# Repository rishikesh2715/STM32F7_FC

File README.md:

# I am going to be working on a new design of this flight controller.

- Removing AT7456E based analog OSD and CVBS routing.
- Targeting modern digital FPV systems.
- Feel free to recommend any changes you wanna see. Just open an issue.

Hoping to have the new hardware done next month if life chills out. 

# STM32F7_Based_FLight-controller
STM32F722RET6 Based Flight Controller with ICM-42688-P IMU, BMP388 Barometer, and much more!

Detailed Specification:
- MCU - STM32F722RET6
- Interial Measurement Unit (IMU) - ICM-42688-P
- Barometer - BMP388
- On-screen Display chip (OSD) - AT7456E
- SPI FLASH - W25Q256JVEIQ (256 Mbit QUAD SPI NOR FLASH)
- 9 V -- 2A Buck Converter - TPS54335ADRCR
- 5V -- 2A Buck Converter - TPS54335ADRCR
- 3.3 V -- 700 mA LDO - AZ1117-3.3

Connectors:
- 4 UARTs
- 3 SPIs
- 1 I2C

This flight controller is directly flashable and configurale via BetaFlight. Make sure to flash the FC with custom CLI file named "IRS_CLI". There is a official tutorial on youtube on how to flash a custom flight controller with a custom cli file.

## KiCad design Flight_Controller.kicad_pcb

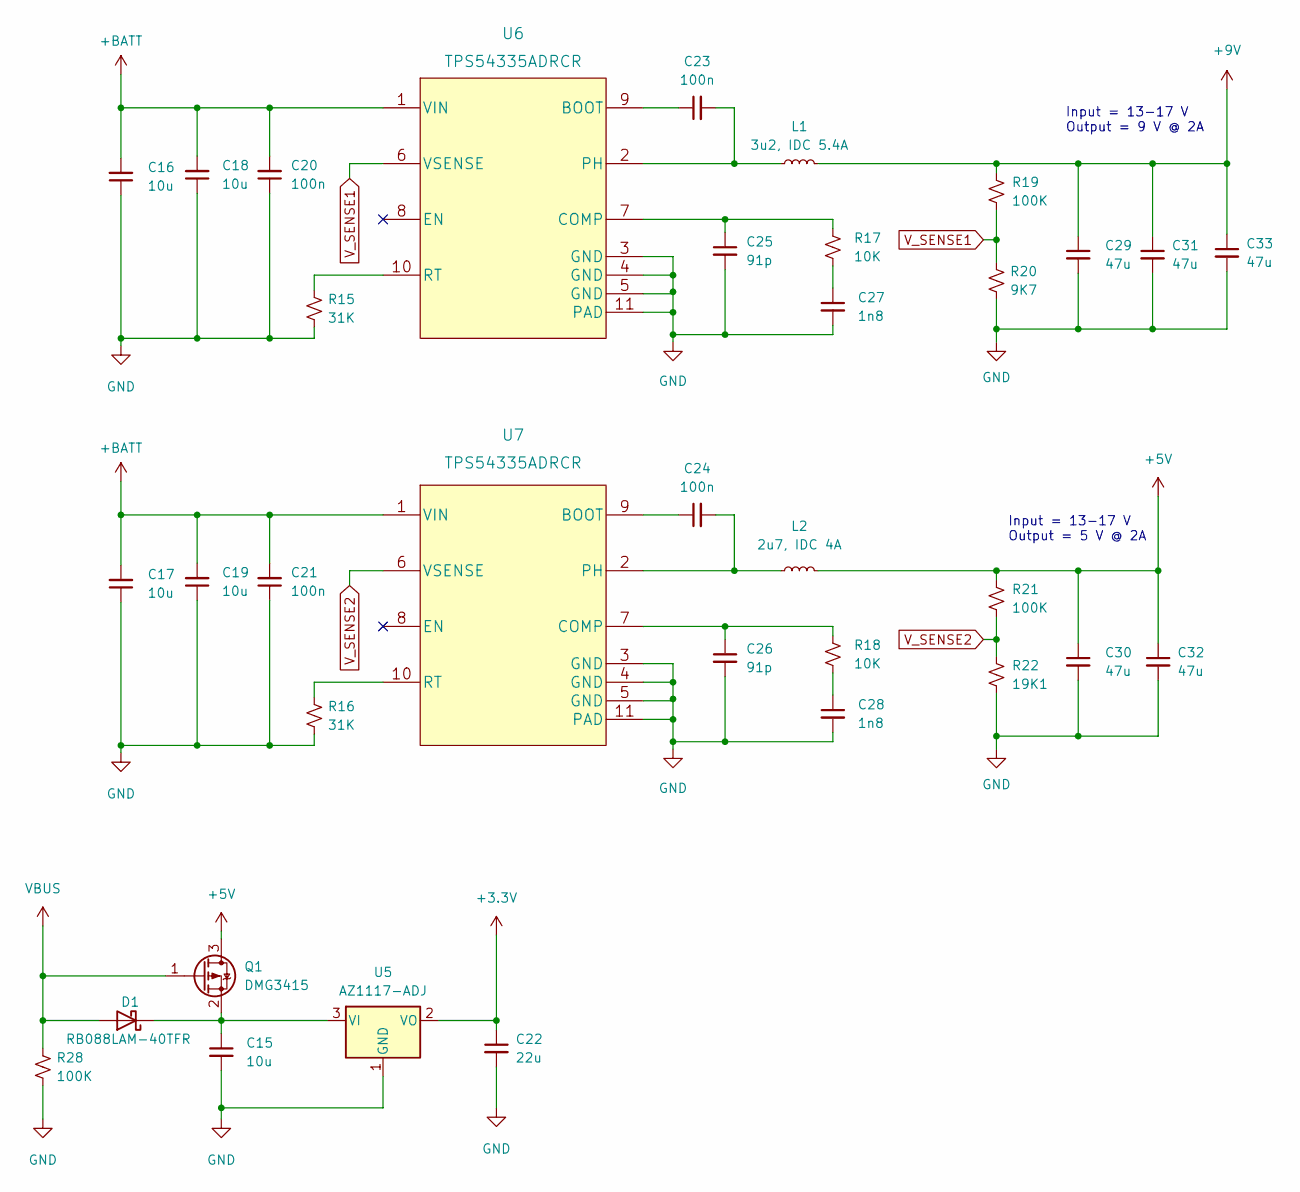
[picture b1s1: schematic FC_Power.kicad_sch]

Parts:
C15, C16, C17, C18, C19: 10u; C_0805_2012Metric
C20, C21, C23, C24: 100n; C_0402_1005Metric
C22: 22u; C_0805_2012Metric
C25, C26: 91p; C_0201_0603Metric
C27, C28: 1n8; C_0603_1608Metric
C29, C30, C31, C32, C33: 47u; C_1210_3225Metric
D1: RB088LAM-40TFR; D_SOD-123
L1: 3u2, IDC 5.4A; MDE0530-6R8M
L2: 2u7, IDC 4A; MDE0530-6R8M
Q1: DMG3415; SOT-23
R15, R16: 31K; R_0402_1005Metric
R17, R18: 10K; R_0402_1005Metric
R19: 100K; R_0402_1005Metric
R20: 9K7; R_0402_1005Metric
R21, R28: 100K; R_0201_0603Metric
R22: 19K1; R_0201_0603Metric
U5: AZ1117-ADJ; SOT-223-3_TabPin2
U6, U7: TPS54335ADRCR

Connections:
+3V3: C22.1, U5.2 (VO); also elsewhere on the board
+5V: C30.1, C32.1, L2.2, Q1.3 (D), R21.1; also elsewhere on the board
+9V: C29.1, C31.1, C33.1, L1.2, R19.1; also elsewhere on the board
+BATT: C16.2, C17.2, C18.2, C19.2, C20.2, C21.2, U6.1 (VIN), U7.1 (VIN); also elsewhere on the board
GND: C15.2, C16.1, C17.1, C18.1, C19.1, C20.1, C21.1, C22.2, C25.2, C26.2, C27.2, C28.2, C29.2, C30.2, C31.2, C32.2, C33.2, R15.2, R16.2, R20.2, R22.2, R28.2, U5.1 (GND), U6.3 (GND), U6.4 (GND), U6.5 (GND), U6.11 (PAD), U7.3 (GND), U7.4 (GND), U7.5 (GND), U7.11 (PAD); also elsewhere on the board
unnamed: C15.1, D1.1 (K), Q1.2 (S), U5.3 (VI)
unnamed: C23.1, U6.9 (BOOT)
unnamed: C23.2, L1.1, U6.2 (PH)
unnamed: C24.1, U7.9 (BOOT)
unnamed: C24.2, L2.1, U7.2 (PH)
unnamed: C25.1, R17.1, U6.7 (COMP)
unnamed: C26.1, R18.1, U7.7 (COMP)
unnamed: C27.1, R17.2
unnamed: C28.1, R18.2
unnamed: R15.1, U6.10 (RT)
unnamed: R16.1, U7.10 (RT)
VBUS: D1.2 (A), Q1.1 (G), R28.1; also elsewhere on the board
V_SENSE1: R19.2, R20.1, U6.6 (VSENSE)
V_SENSE2: R21.2, R22.1, U7.6 (VSENSE)

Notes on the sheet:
Input = 13-17 V Output = 9 V @ 2A
Input = 13-17 V Output = 5 V @ 2A

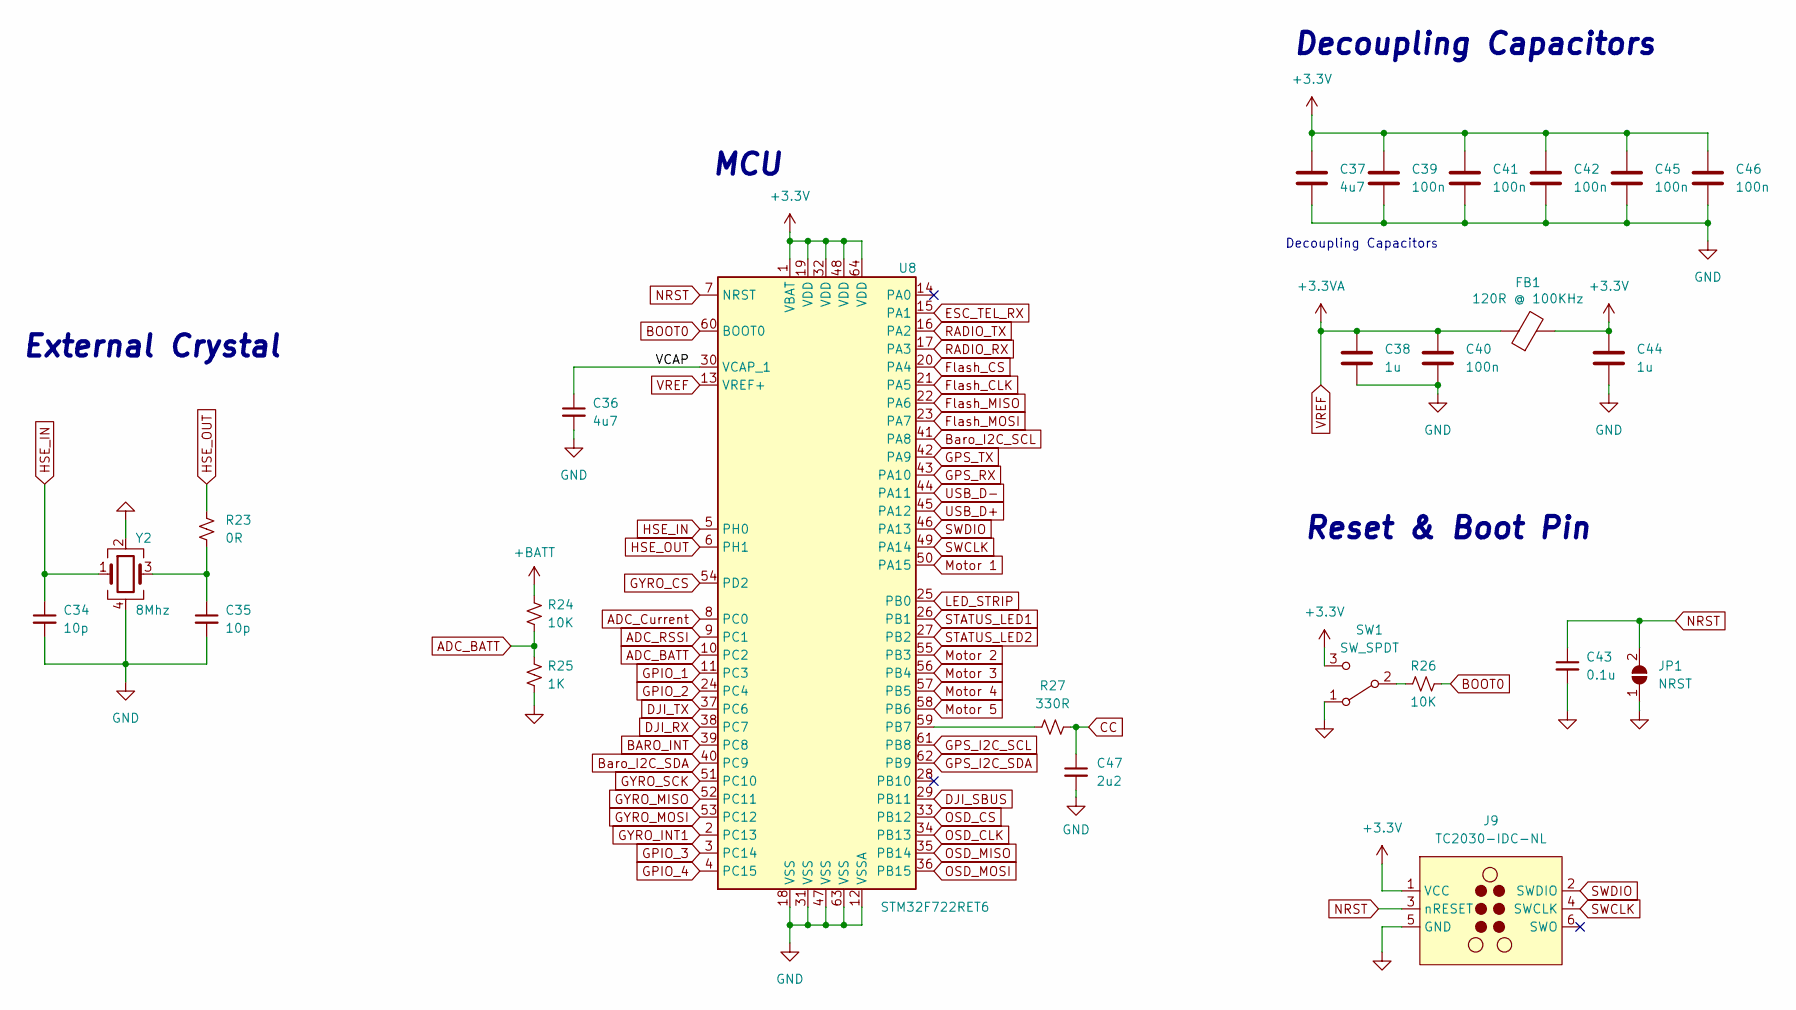
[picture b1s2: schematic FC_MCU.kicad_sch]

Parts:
C34, C35: 10p; C_0402_1005Metric
C36: 4u7; C_0603_1608Metric
C37: 4u7; C_0402_1005Metric
C38, C44: 1u; C_0402_1005Metric
C39, C40, C41, C42, C45, C46: 100n; C_0201_0603Metric
C43: 0.1u; C_0402_1005Metric
C47: 2u2; C_0603_1608Metric
FB1: 120R @ 100KHz; R_0603_1608Metric
J9: TC2030-IDC-NL; Tag-Connect_TC2030-IDC-NL_2x03_P1.27mm_Vertical
JP1: NRST; SolderJumper-2_P1.3mm_Open_TrianglePad1.0x1.5mm
R23: 0R; R_0402_1005Metric
R24: 10K; R_0201_0603Metric
R25: 1K; R_0201_0603Metric
R26: 10K; R_0402_1005Metric
R27: 330R; R_0603_1608Metric
SW1: SW_SPDT; SSSS810701
U8: STM32F722RET6; LQFP-64_10x10mm_P0.5mm
Y2: 8Mhz; Crystal_SMD_3225-4Pin_3.2x2.5mm

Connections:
+3V3: C37.1, C39.1, C41.1, C42.1, C44.1, C45.1, C46.1, FB1.2, J9.1 (VCC), SW1.3 (C), U8.1 (VBAT), U8.19 (VDD), U8.32 (VDD), U8.48 (VDD), U8.64 (VDD); also elsewhere on the board
+BATT: R24.1; also elsewhere on the board
/MCU/VCAP: C36.1, U8.30 (VCAP_1)
ADC_BATT: R24.2, R25.1, U8.10 (PC2)
ADC_Current: U8.8 (PC0); also elsewhere on the board
ADC_RSSI: U8.9 (PC1)
BARO_INT: U8.39 (PC8); also elsewhere on the board
BOOT0: R26.2, U8.60 (BOOT0)
Baro_I2C_SCL: U8.41 (PA8); also elsewhere on the board
Baro_I2C_SDA: U8.40 (PC9); also elsewhere on the board
CC: C47.1, R27.2; also elsewhere on the board
DJI_RX: U8.38 (PC7); also elsewhere on the board
DJI_SBUS: U8.29 (PB11); also elsewhere on the board
DJI_TX: U8.37 (PC6); also elsewhere on the board
ESC_TEL_RX: U8.15 (PA1); also elsewhere on the board
Flash_CLK: U8.21 (PA5); also elsewhere on the board
Flash_CS: U8.20 (PA4); also elsewhere on the board
Flash_MISO: U8.22 (PA6); also elsewhere on the board
Flash_MOSI: U8.23 (PA7); also elsewhere on the board
GND: C34.2, C35.2, C36.2, C37.2, C38.2, C39.2, C40.2, C41.2, C42.2, C43.2, C44.2, C45.2, C46.2, C47.2, J9.5 (GND), JP1.1 (A), R25.2, SW1.1 (A), U8.12 (VSSA), U8.18 (VSS), U8.31 (VSS), U8.47 (VSS), U8.63 (VSS), Y2.2, Y2.4; also elsewhere on the board
GPIO_1: U8.11 (PC3); also elsewhere on the board
GPIO_2: U8.24 (PC4); also elsewhere on the board
GPIO_3: U8.3 (PC14); also elsewhere on the board
GPIO_4: U8.4 (PC15); also elsewhere on the board
GPS_I2C_SCL: U8.61 (PB8); also elsewhere on the board
GPS_I2C_SDA: U8.62 (PB9); also elsewhere on the board
GPS_RX: U8.43 (PA10); also elsewhere on the board
GPS_TX: U8.42 (PA9); also elsewhere on the board
GYRO_CS: U8.54 (PD2); also elsewhere on the board
GYRO_INT1: U8.2 (PC13); also elsewhere on the board
GYRO_MISO: U8.52 (PC11); also elsewhere on the board
GYRO_MOSI: U8.53 (PC12); also elsewhere on the board
GYRO_SCK: U8.51 (PC10); also elsewhere on the board
HSE_IN: C34.1, U8.5 (PH0), Y2.1
HSE_OUT: R23.1, U8.6 (PH1)
LED_STRIP: U8.25 (PB0); also elsewhere on the board
Motor 1: U8.50 (PA15); also elsewhere on the board
Motor 2: U8.55 (PB3); also elsewhere on the board
Motor 3: U8.56 (PB4); also elsewhere on the board
Motor 4: U8.57 (PB5); also elsewhere on the board
Motor 5: U8.58 (PB6); also elsewhere on the board
NRST: C43.1, J9.3 (nRESET), JP1.2 (B), U8.7 (NRST)
unnamed: C35.1, R23.2, Y2.3
unnamed: R26.1, SW1.2 (B)
unnamed: R27.1, U8.59 (PB7)
OSD_CLK: U8.34 (PB13); also elsewhere on the board
OSD_CS: U8.33 (PB12); also elsewhere on the board
OSD_MISO: U8.35 (PB14); also elsewhere on the board
OSD_MOSI: U8.36 (PB15); also elsewhere on the board
RADIO_RX: U8.17 (PA3); also elsewhere on the board
RADIO_TX: U8.16 (PA2); also elsewhere on the board
STATUS_LED1: U8.26 (PB1); also elsewhere on the board
STATUS_LED2: U8.27 (PB2); also elsewhere on the board
SWCLK: J9.4 (SWCLK), U8.49 (PA14)
SWDIO: J9.2 (SWDIO), U8.46 (PA13)
USB_D+: U8.45 (PA12); also elsewhere on the board
USB_D-: U8.44 (PA11); also elsewhere on the board
VREF: C38.1, C40.1, FB1.1, U8.13 (VREF+)

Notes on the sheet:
External Crystal
MCU
Decoupling Capacitors
Reset & Boot Pin

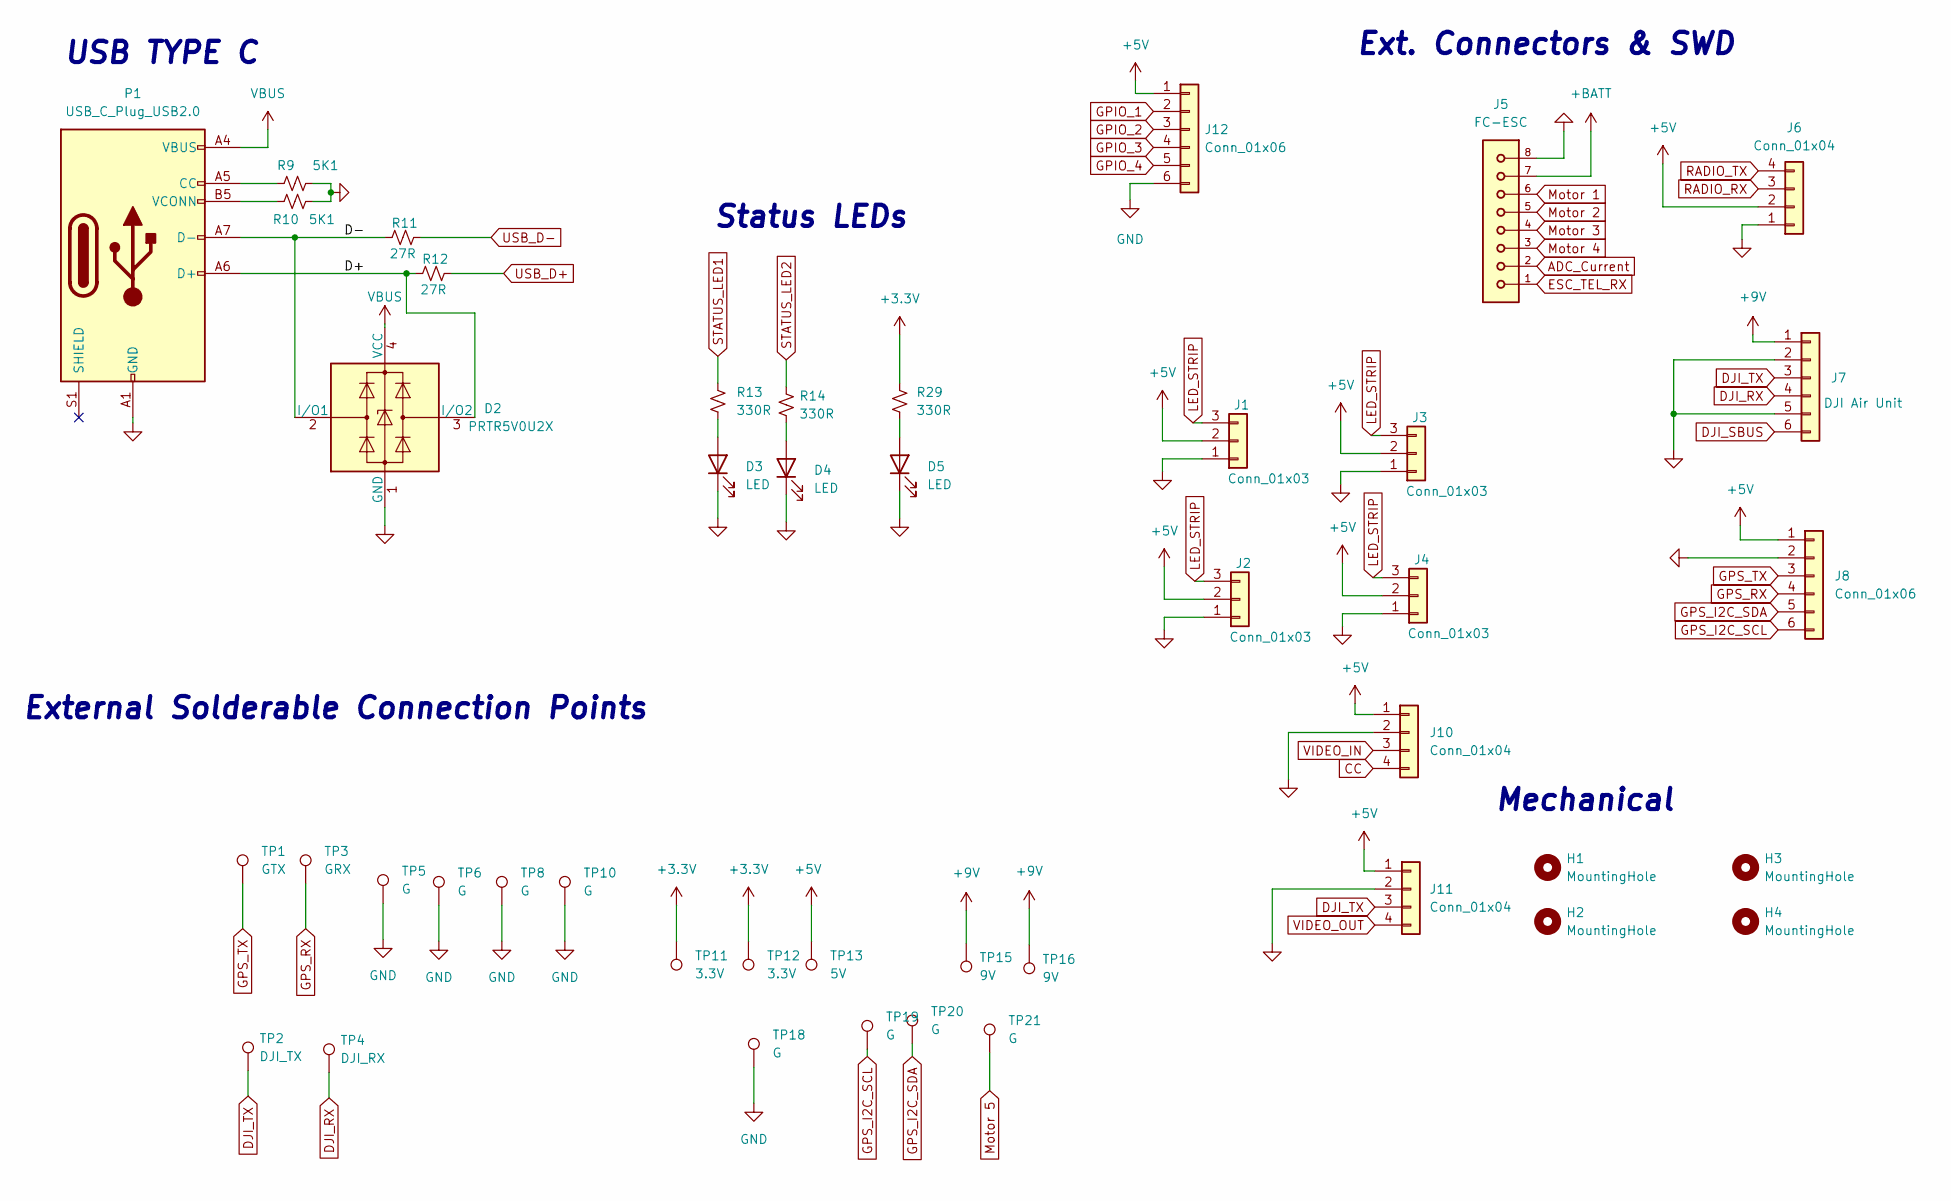
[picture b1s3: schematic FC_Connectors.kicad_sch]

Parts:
D2: PRTR5V0U2X; SOT-143
D3, D4, D5: LED; LED_0402_1005Metric
H1, H2, H3, H4: MountingHole; MountingHole_2.2mm_M2_Pad_Via
J1, J2, J3, J4: Conn_01x03; JST_SH_SM03B-SRSS-TB_1x03-1MP_P1.00mm_Horizontal
J5: FC-ESC; JST_SH_SM08B-SRSS-TB_1x08-1MP_P1.00mm_Horizontal
J6, J10, J11: Conn_01x04; JST_SH_SM04B-SRSS-TB_1x04-1MP_P1.00mm_Horizontal
J7: DJI Air Unit; JST_SH_SM06B-SRSS-TB_1x06-1MP_P1.00mm_Horizontal
J8, J12: Conn_01x06; JST_SH_SM06B-SRSS-TB_1x06-1MP_P1.00mm_Horizontal
P1: USB_C_Plug_USB2.0; USB4110GFA
R9, R10: 5K1; R_0201_0603Metric
R11, R12: 27R; R_0201_0603Metric
R13, R14, R29: 330R; R_0402_1005Metric
TP1: GTX; Solderable Point
TP2: DJI_TX; Solderable Point
TP3: GRX; Solderable Point
TP4: DJI_RX; Solderable Point
TP5, TP6, TP8, TP10, TP18, TP19, TP20, TP21: G; Solderable Point
TP11, TP12: 3.3V; Solderable Point
TP13: 5V; Solderable Point
TP15, TP16: 9V; Solderable Point

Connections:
+3V3: R29.1, TP11.1, TP12.1; also elsewhere on the board
+5V: J1.2, J2.2, J3.2, J4.2, J6.2, J8.1, J10.1, J11.1, J12.1, TP13.1; also elsewhere on the board
+9V: J7.1, TP15.1, TP16.1; also elsewhere on the board
+BATT: J5.7; also elsewhere on the board
/Connectors/D+: D2.3 (I/O2), P1.A6 (D+), R12.1
/Connectors/D-: D2.2 (I/O1), P1.A7 (D-), R11.1
ADC_Current: J5.2; also elsewhere on the board
CC: J10.4; also elsewhere on the board
DJI_RX: J7.4, TP4.1; also elsewhere on the board
DJI_SBUS: J7.6; also elsewhere on the board
DJI_TX: J7.3, J11.3, TP2.1; also elsewhere on the board
ESC_TEL_RX: J5.1; also elsewhere on the board
GND: D2.1 (GND), D3.1 (K), D4.1 (K), D5.1 (K), J1.1, J2.1, J3.1, J4.1, J5.8, J6.1, J7.2, J7.5, J8.2, J10.2, J11.2, J12.6, P1.A1 (GND), P1.A12 (GND), P1.B1 (GND), P1.B12 (GND), R9.1, R10.2, TP5.1, TP6.1, TP8.1, TP10.1, TP18.1; also elsewhere on the board
GPIO_1: J12.2; also elsewhere on the board
GPIO_2: J12.3; also elsewhere on the board
GPIO_3: J12.4; also elsewhere on the board
GPIO_4: J12.5; also elsewhere on the board
GPS_I2C_SCL: J8.6, TP19.1; also elsewhere on the board
GPS_I2C_SDA: J8.5, TP20.1; also elsewhere on the board
GPS_RX: J8.4, TP3.1; also elsewhere on the board
GPS_TX: J8.3, TP1.1; also elsewhere on the board
LED_STRIP: J1.3, J2.3, J3.3, J4.3; also elsewhere on the board
Motor 1: J5.6; also elsewhere on the board
Motor 2: J5.5; also elsewhere on the board
Motor 3: J5.4; also elsewhere on the board
Motor 4: J5.3; also elsewhere on the board
Motor 5: TP21.1; also elsewhere on the board
unnamed: D3.2 (A), R13.2
unnamed: D4.2 (A), R14.2
unnamed: D5.2 (A), R29.2
unnamed: P1.A5 (CC), R9.2
unnamed: P1.B5 (VCONN), R10.1
RADIO_RX: J6.3; also elsewhere on the board
RADIO_TX: J6.4; also elsewhere on the board
STATUS_LED1: R13.1; also elsewhere on the board
STATUS_LED2: R14.1; also elsewhere on the board
USB_D+: R12.2; also elsewhere on the board
USB_D-: R11.2; also elsewhere on the board
VBUS: D2.4 (VCC), P1.A4 (VBUS), P1.A9 (VBUS), P1.B4 (VBUS), P1.B9 (VBUS); also elsewhere on the board
VIDEO_IN: J10.3; also elsewhere on the board
VIDEO_OUT: J11.4; also elsewhere on the board

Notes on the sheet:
USB TYPE C
Status LEDs
Ext. Connectors & SWD
External Solderable Connection Points
Mechanical

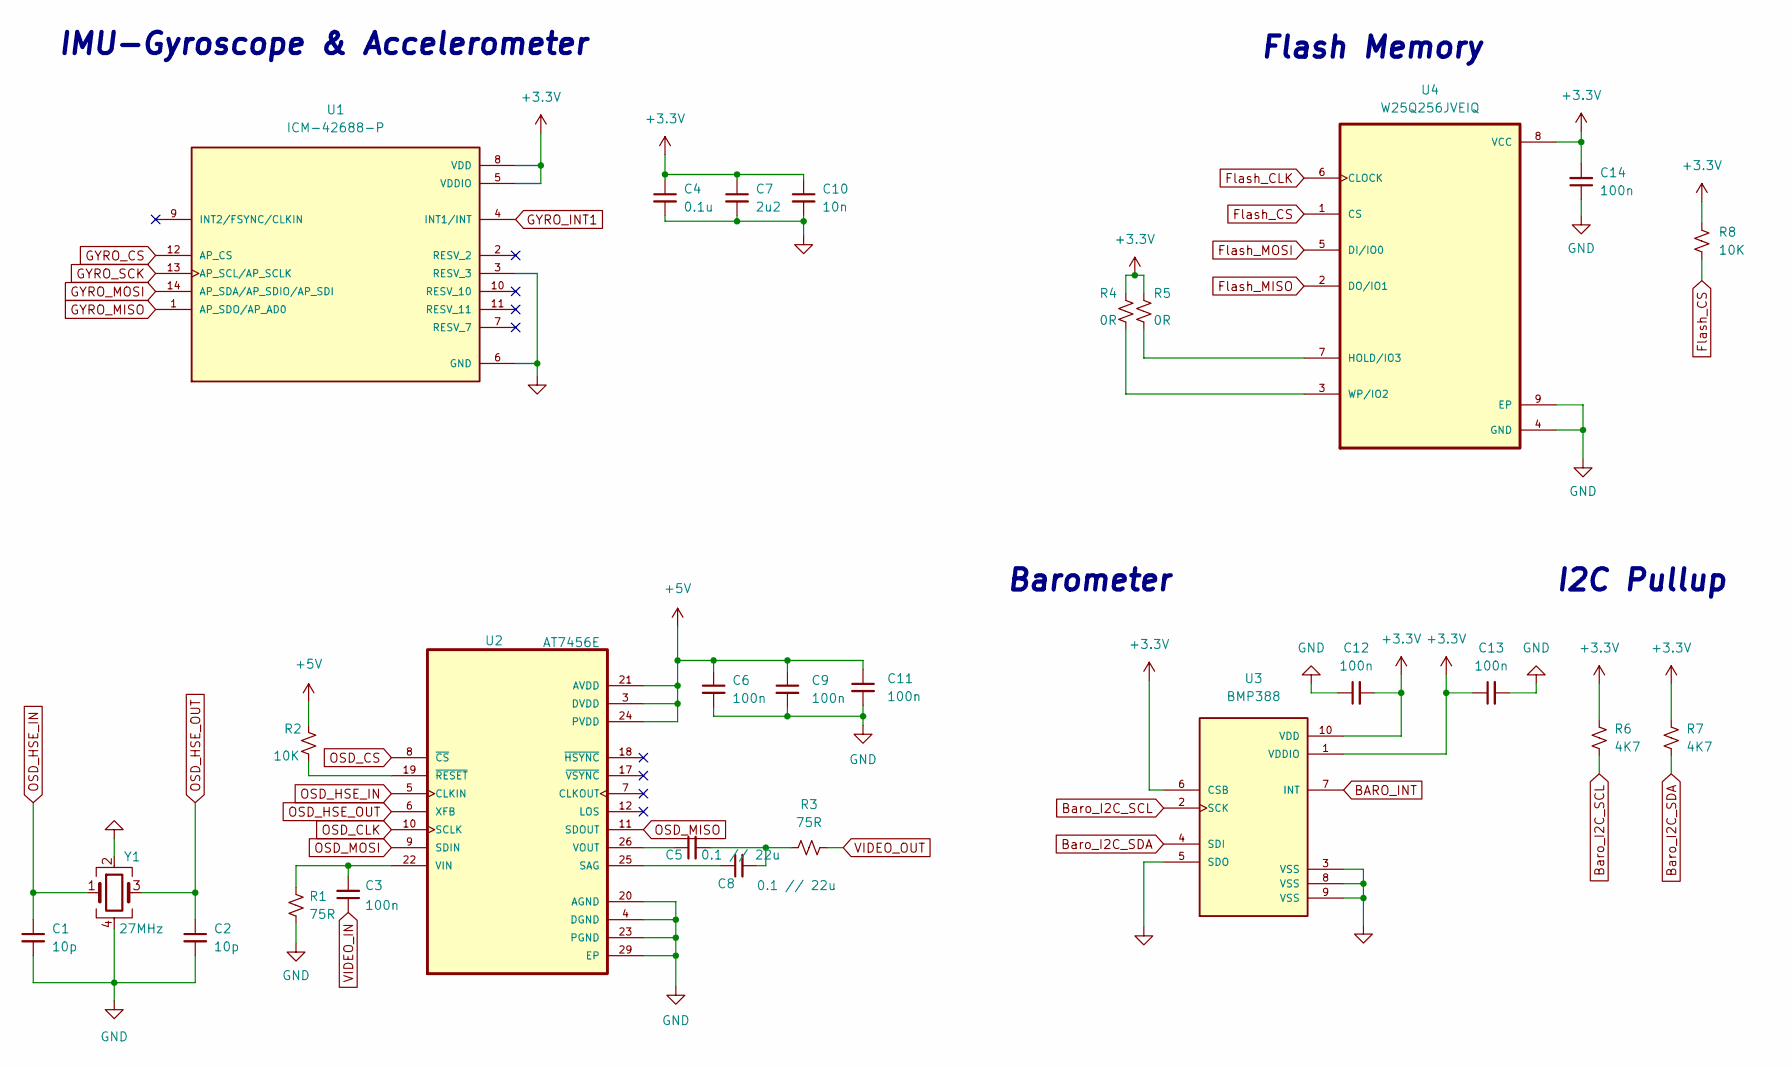
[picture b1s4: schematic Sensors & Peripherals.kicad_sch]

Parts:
C1, C2: 10p; C_0201_0603Metric
C3, C6, C9, C11, C12, C13: 100n; C_0201_0603Metric
C4: 0.1u; C_0402_1005Metric
C5, C8: 0.1 // 22u; C_0201_0603Metric
C7: 2u2; C_0603_1608Metric
C10: 10n; C_0201_0603Metric
C14: 100n; C_0402_1005Metric
R1, R3: 75R; R_0201_0603Metric
R2, R8: 10K; R_0201_0603Metric
R4, R5: 0R; R_0201_0603Metric
R6, R7: 4K7; R_0201_0603Metric
U1: ICM-42688-P; ICP-42688-P; PARTREV 1.2
U2: AT7456E; SOP65P637X110-28N
U3: BMP388; PARTREV 1.1
U4: W25Q256JVEIQ; SON127P600X800X80-9N
Y1: 27MHz; Crystal_SMD_3225-4Pin_3.2x2.5mm

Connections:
+3V3: C4.1, C7.1, C10.1, C12.2, C13.1, C14.2, R4.1, R5.1, R6.1, R7.1, R8.1, U1.5 (VDDIO), U1.8 (VDD), U3.1 (VDDIO), U3.6 (CSB), U3.10 (VDD), U4.8 (VCC); also elsewhere on the board
+5V: C6.1, C9.1, C11.1, R2.2, U2.3 (DVDD), U2.21 (AVDD), U2.24 (PVDD); also elsewhere on the board
BARO_INT: U3.7 (INT); also elsewhere on the board
Baro_I2C_SCL: R6.2, U3.2 (SCK); also elsewhere on the board
Baro_I2C_SDA: R7.2, U3.4 (SDI); also elsewhere on the board
Flash_CLK: U4.6 (CLOCK); also elsewhere on the board
Flash_CS: R8.2, U4.1 (CS); also elsewhere on the board
Flash_MISO: U4.2 (DO/IO1); also elsewhere on the board
Flash_MOSI: U4.5 (DI/IO0); also elsewhere on the board
GND: C1.2, C2.2, C4.2, C6.2, C7.2, C9.2, C10.2, C11.2, C12.1, C13.2, C14.1, R1.2, U1.3 (RESV_3), U1.6 (GND), U2.4 (DGND), U2.20 (AGND), U2.23 (PGND), U2.29 (EP), U3.3 (VSS), U3.5 (SDO), U3.8 (VSS), U3.9 (VSS), U4.4 (GND), U4.9 (EP), Y1.2, Y1.4; also elsewhere on the board
GYRO_CS: U1.12 (AP_CS); also elsewhere on the board
GYRO_INT1: U1.4 (INT1/INT); also elsewhere on the board
GYRO_MISO: U1.1 (AP_SDO/AP_AD0); also elsewhere on the board
GYRO_MOSI: U1.14 (AP_SDA/AP_SDIO/AP_SDI); also elsewhere on the board
GYRO_SCK: U1.13 (AP_SCL/AP_SCLK); also elsewhere on the board
unnamed: C3.2, R1.1, U2.22 (VIN)
unnamed: C5.1, U2.26 (VOUT)
unnamed: C5.2, C8.2, R3.1
unnamed: C8.1, U2.25 (SAG)
unnamed: R2.1, U2.19 (~RESET)
unnamed: R4.2, U4.3 (WP/IO2)
unnamed: R5.2, U4.7 (HOLD/IO3)
OSD_CLK: U2.10 (SCLK); also elsewhere on the board
OSD_CS: U2.8 (~CS); also elsewhere on the board
OSD_HSE_IN: C1.1, U2.5 (CLKIN), Y1.1
OSD_HSE_OUT: C2.1, U2.6 (XFB), Y1.3
OSD_MISO: U2.11 (SDOUT); also elsewhere on the board
OSD_MOSI: U2.9 (SDIN); also elsewhere on the board
VIDEO_IN: C3.1; also elsewhere on the board
VIDEO_OUT: R3.2; also elsewhere on the board

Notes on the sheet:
I2C Pullup
Flash Memory
IMU-Gyroscope & Accelerometer
Barometer

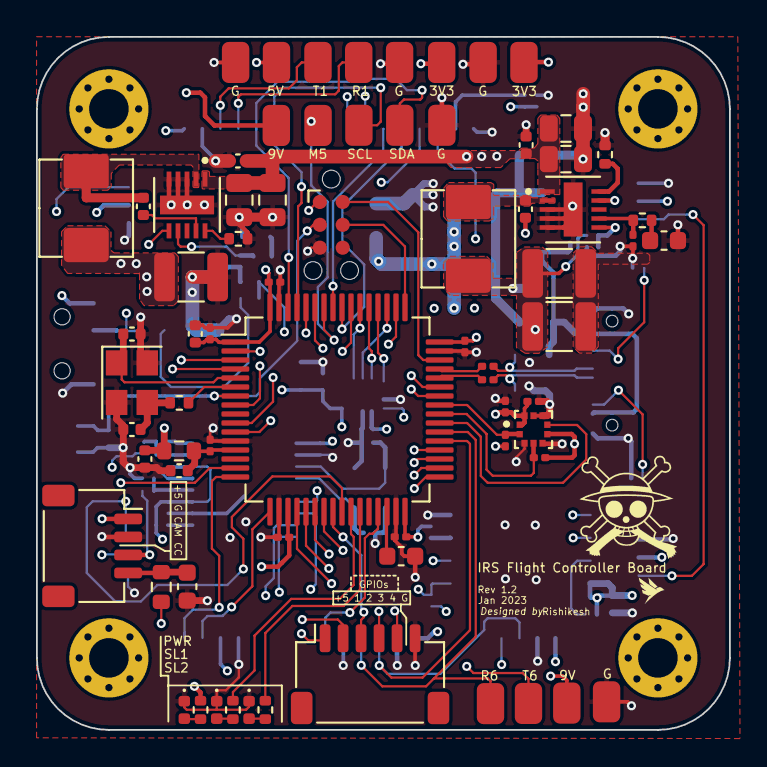
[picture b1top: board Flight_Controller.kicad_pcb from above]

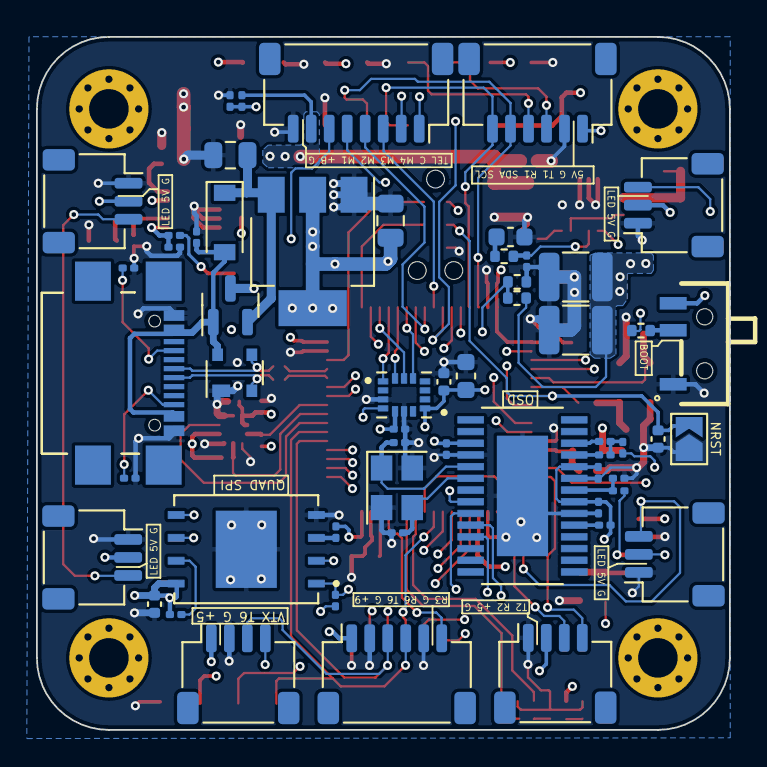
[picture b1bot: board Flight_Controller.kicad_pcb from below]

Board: 8 copper layers, 38.5 x 38.5 mm, 131 parts (56 on the bottom side), 91 nets.

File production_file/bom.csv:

Designator,Footprint,Quantity,Value,LCSC Part #
TP19,Solderable Point,1,G,
TP6,Solderable Point,1,G,
TP5,Solderable Point,1,G,
D3,LED_0402_1005Metric,1,LED,
C39,C_0201_0603Metric,1,100n,
TP4,Solderable Point,1,DJI_RX,
TP8,Solderable Point,1,G,
TP12,Solderable Point,1,3.3V,
TP11,Solderable Point,1,3.3V,
TP10,Solderable Point,1,G,
C46,C_0201_0603Metric,1,100n,
FB1,R_0603_1608Metric,1,120R,
R14,R_0402_1005Metric,1,550R,
H3,MountingHole_2.2mm_M2_Pad_Via,1,MountingHole,
R6,R_0201_0603Metric,1,4K7,
U8,LQFP-64_10x10mm_P0.5mm,1,STM32F722RET6,
TP20,Solderable Point,1,G,
C44,C_0402_1005Metric,1,1u,
TP21,Solderable Point,1,G,
C41,C_0201_0603Metric,1,100n,
C17,C_0805_2012Metric,1,10u,
R18,R_0402_1005Metric,1,10K,
H4,MountingHole_2.2mm_M2_Pad_Via,1,MountingHole,
C38,C_0402_1005Metric,1,1u,
R29,R_0402_1005Metric,1,550R,
L1,MDE0530-6R8M,1,"3u2, IDC 5.4A",
C16,C_0805_2012Metric,1,10u,
C28,C_0603_1608Metric,1,1n8,
C19,C_0805_2012Metric,1,10u,
H1,MountingHole_2.2mm_M2_Pad_Via,1,MountingHole,
C32,C_1210_3225Metric,1,47u,
R27,R_0603_1608Metric,1,330R,
C45,C_0201_0603Metric,1,100n,
TP18,Solderable Point,1,G,
TP13,Solderable Point,1,5V,
R16,R_0402_1005Metric,1,31K,
R15,R_0402_1005Metric,1,31K,
C34,C_0402_1005Metric,1,10p,
D4,LED_0402_1005Metric,1,LED,
R11,R_0201_0603Metric,1,27R,
C12,C_0201_0603Metric,1,100n,
R7,R_0201_0603Metric,1,4K7,
C35,C_0402_1005Metric,1,10p,
TP16,Solderable Point,1,9V,
C13,C_0201_0603Metric,1,100n,
C42,C_0201_0603Metric,1,100n,
J10,JST_SH_SM04B-SRSS-TB_1x04-1MP_P1.00mm_Horizontal,1,Conn_01x04,
TP2,Solderable Point,1,DJI_TX,
R12,R_0201_0603Metric,1,27R,
J9,Tag-Connect_TC2030-IDC-NL_2x03_P1.27mm_Vertical,1,TC2030-IDC-NL,
TP3,Solderable Point,1,GRX,
C30,C_1210_3225Metric,1,47u,
D5,LED_0402_1005Metric,1,LED,
L2,MDE0530-6R8M,1,"2u7, IDC 4A",
H2,MountingHole_2.2mm_M2_Pad_Via,1,MountingHole,
C23,C_0402_1005Metric,1,100n,
TP1,Solderable Point,1,GTX,
C24,C_0402_1005Metric,1,100n,
R13,R_0402_1005Metric,1,550R,
C47,C_0603_1608Metric,1,2u2,
C36,C_0603_1608Metric,1,4u7,
C33,C_1210_3225Metric,1,47u,
C40,C_0201_0603Metric,1,100n,
U7,TPS54335ADRCR,1,TPS54335ADRCR,
C37,C_0402_1005Metric,1,10u,
R23,R_0402_1005Metric,1,0R,
Y2,Crystal_SMD_3225-4Pin_3.2x2.5mm,1,8Mhz,
U6,TPS54335ADRCR,1,TPS54335ADRCR,
TP15,Solderable Point,1,9V,
C21,C_0402_1005Metric,1,100n,
C20,C_0402_1005Metric,1,100n,
C26,C_0201_0603Metric,1,91p,
C18,C_0805_2012Metric,1,10u,
U3,BMP388,1,BMP388,
J12,JST_SH_SM06B-SRSS-TB_1x06-1MP_P1.00mm_Horizontal,1,Conn_01x06,
C10,C_0201_0603Metric,1,10n,
C22,C_0805_2012Metric,1,22u,
C1,C_0201_0603Metric,1,10p,
J5,JST_SH_SM08B-SRSS-TB_1x08-1MP_P1.00mm_Horizontal,1,FC-ESC,
C2,C_0201_0603Metric,1,10p,
R20,R_0402_1005Metric,1,9K7,
R1,R_0201_0603Metric,1,75R,
R5,R_0201_0603Metric,1,0R,
C27,C_0603_1608Metric,1,1n8,
C8,C_0201_0603Metric,1,22u,
J8,JST_SH_SM06B-SRSS-TB_1x06-1MP_P1.00mm_Horizontal,1,Conn_01x06,
Y1,Crystal_SMD_3225-4Pin_3.2x2.5mm,1,27MHz,
R25,R_0201_0603Metric,1,1K,
C15,C_0805_2012Metric,1,10u,
Q1,SOT-23,1,DMG3415,
C3,C_0201_0603Metric,1,100n,
R19,R_0402_1005Metric,1,100K,
U4,SON127P600X800X80-9N,1,W25Q256JVEIQ,
J2,JST_SH_SM03B-SRSS-TB_1x03-1MP_P1.00mm_Horizontal,1,Conn_01x03,
C43,C_0402_1005Metric,1,0.1u,
R3,R_0201_0603Metric,1,75R,
C6,C_0201_0603Metric,1,100n,
R2,R_0201_0603Metric,1,10K,
C5,C_0201_0603Metric,1,22u,
C25,C_0201_0603Metric,1,91p,
R10,R_0201_0603Metric,1,5K1,
SW1,SSSS810701,1,SW_SPDT,
J1,JST_SH_SM03B-SRSS-TB_1x03-1MP_P1.00mm_Horizontal,1,Conn_01x03,
C4,C_0402_1005Metric,1,0.1u,
U5,SOT-223-3_TabPin2,1,AZ1117-ADJ,
J6,JST_SH_SM04B-SRSS-TB_1x04-1MP_P1.00mm_Horizontal,1,Conn_01x04,
C9,C_0201_0603Metric,1,100n,
J3,JST_SH_SM03B-SRSS-TB_1x03-1MP_P1.00mm_Horizontal,1,Conn_01x03,
R22,R_0201_0603Metric,1,19K1,
D1,D_SOD-123,1,RB088LAM-40TFR,
R9,R_0201_0603Metric,1,5K1,
R26,R_0402_1005Metric,1,10K,
C7,C_0603_1608Metric,1,2u2,
R17,R_0402_1005Metric,1,10K,
C29,C_1210_3225Metric,1,47u,
C14,C_0402_1005Metric,1,100n,
C11,C_0201_0603Metric,1,100n,
R24,R_0201_0603Metric,1,10K,
C31,C_1210_3225Metric,1,47u,
J4,JST_SH_SM03B-SRSS-TB_1x03-1MP_P1.00mm_Horizontal,1,Conn_01x03,
J11,JST_SH_SM04B-SRSS-TB_1x04-1MP_P1.00mm_Horizontal,1,Conn_01x04,
R8,R_0201_0603Metric,1,10K,
D2,SOT-143,1,PRTR5V0U2X,
JP1,SolderJumper-2_P1.3mm_Open_TrianglePad1.0x1.5mm,1,NRST,
U2,SOP65P637X110-28N,1,AT7456E,
R21,R_0201_0603Metric,1,100K,
J7,JST_SH_SM06B-SRSS-TB_1x06-1MP_P1.00mm_Horizontal,1,DJI Air Unit,
P1,USB4110GFA,1,USB_C_Plug_USB2.0,
R4,R_0201_0603Metric,1,0R,
R28,R_0201_0603Metric,1,100K,
U1,ICP-42688-P,1,ICM-42688-P,

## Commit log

2023-03-04 Create bom
2023-03-04 Create gerber
2025-12-18 Update to this design coming soon!!
2026-02-17 Edit README
    I was drunk
